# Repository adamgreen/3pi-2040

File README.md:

<br>
My experiments with [Pololu's 3pi+ 2040 robot kit](https://www.pololu.com/product/5004) that was [released on March 7th, 2023](https://www.pololu.com/blog/937/introducing-the-3pi-plus-2040-robot).

## Archived February 4th, 2024
I learned a lot while working on this little bot over the last year. I gained an even better appreciation for the RP2040 microcontroller, got some great mechanical/electronic build ideas from Pololu's cool design, I got the opportunity to port an Arduino library to it, and it even kick started my [MRI-SWD Debug probe](https://github.com/adamgreen/mri-swd#readme) project that I am still actively working on. I think this is a good point to bring my work with this bot itself to an end and I am therefore marking this repository as archived. I will concentrate on other projects instead.

## Notable Page Sections
* [Using Arduino with the 3pi+ 2040](#arduino--3pi-2040)
* [My 3pi+ 2040 Arduino Library](#pololu3piplus2040-arduino-library-port-completed)
* [Debugging 3pi+ 2040 with the Segger J-Link](#debugging-the-3pi-with-segger-j-link)
* [My Notes for Pololu](#my-notes-for-pololu)

## Pololu Links
* [3pi+ 2040 Robot Kit with 30:1 MP Motors (Standard Edition Kit) Pololu Product Page](https://www.pololu.com/product/5004)
* [Pololu 3pi+ 2040 User’s Guide](https://www.pololu.com/docs/0J86)
* [Pololu 3pi+ 2040 Robot Libraries and Example Code on GitHub](https://github.com/pololu/pololu-3pi-2040-robot)

---
## June 6th, 2023
### MRI-SWD Debug Probe Progress
It's been awhile since I had anything to post here but that doesn't mean that I haven't been making progress on a 3π+ 2040 related project. I have spent the last month working on my [MRI-SWD Debug probe](https://github.com/adamgreen/mri-swd#readme). The goal is to use this probe to wirelessly program and debug the RP2040 microcontroller on the 3π+ 2040 robot.

I have the initial prototype far enough along that it can perform basic programming and debugging of RP2040 microcontrollers but only in a breadboard setup. The following shows a sample run of GDB using the programming functionality of the debug probe as it currently exists:

```console
$ arm-none-eabi-gdb -ex "set target-charset ASCII" -ex "set print pretty on" -ex "set remotelogfile mri.log" -ex "target remote 10.0.0.12:2331" -ex "set mem inaccessible-by-default off" test.elf

GNU gdb (Arm GNU Toolchain 12.2 (Build arm-12-mpacbti.34)) 13.1.90.20230307-git
Copyright (C) 2023 Free Software Foundation, Inc.
License GPLv3+: GNU GPL version 3 or later <http://gnu.org/licenses/gpl.html>
This is free software: you are free to change and redistribute it.
There is NO WARRANTY, to the extent permitted by law.
Type "show copying" and "show warranty" for details.
This GDB was configured as "--host=aarch64-apple-darwin20.6.0 --target=arm-none-eabi".
Type "show configuration" for configuration details.
For bug reporting instructions, please see:
<https://bugs.linaro.org/>.
Find the GDB manual and other documentation resources online at:
    <http://www.gnu.org/software/gdb/documentation/>.

For help, type "help".
Type "apropos word" to search for commands related to "word"...
Reading symbols from build/QuadratureDecoder.elf...
Remote debugging using 10.0.0.12:2331
get_absolute_time () at /depots/QuadratureDecoder/pico-sdk/src/common/pico_time/include/pico/time.h:63
63	    update_us_since_boot(&t, time_us_64());
(gdb) load
Loading section .boot2, size 0x100 lma 0x10000000
Loading section .text, size 0x7130 lma 0x10000100
Loading section .rodata, size 0x17c8 lma 0x10007230
Loading section .binary_info, size 0x1c lma 0x100089f8
Loading section .data, size 0x2dc lma 0x10008a14
Start address 0x100001e8, load size 36080
Transfer rate: 47 KB/sec, 5154 bytes/write.
```

### UART Port Adapter

Now that I have the **mri-swd** probe working in a breadboard setup, I want to start down the path of designing PCBs which will allow the debug probe to be attached easily to the 3π+ 2040 robot itself. With that in mind, I have started designing a PCB that attaches to the **Mid Expansion Header** on the 3π+ 2040:
* This PCB routes the UART0 Rx, UART0 Tx, and Ground lines from the 3π+ header to a 6-pin 0.1" header which is compatible with FTDI USB to serial converters, such as this [one from Adafruit](https://www.adafruit.com/product/284).
* This PCB also optionally allows the 3.3V power line of the 3π+ 2040 robot to be connected to the 6-pin FTDI compatible header. Normally this connection isn't needed as the robot will be powered from its own batteries or USB:
  * If used with an actual FTDI adapter then the 3.3V solder jumper on the PCB should be left open circuit so that both the robot and the FTDI adapter don't try to both apply power to the same pin.
  * I also plan to use this 6-pin header for powering and mounting the final **mri-swd** debug probe hardware to the robot. When used for this scenario, the 3.3V solder jumper should be shorted so that the robot's power supply can be used to power the debug hardware as well. Having the **mri-swd** debug probe connected to this header will also allow the probe to expose the UART0 serial traffic on a second WiFi socket.
* The design has been sent off to [OSHPark](https://oshpark.com). I will post again once the PCB arrives and I have it soldered up.

---
## April 22nd, 2023

I received the PCBs from [OSHPark](https://oshpark.com) for my [Debug Port Adapter](hardware/DebugPortAdapter/) this week. A day later I soldered one of them up and now I have a much easier way to connect the [Segger J-Link Debugger](https://www.adafruit.com/product/1369) to my 3π+ 2040. As can be seen above it contains:
* A 10-pin connector that can accept standard SWD debug cables.
* A reset button which is easier to access than the original now under this adapter.
* A power LED which is easier to see than the original now under this adapter.

---
## April 12th, 2023
### Pololu3piPlus2040 Arduino Library Updated to 0.1.2
Over the last week, I have released another 2 updates to the [3π+ 2040 Arduino Library](https://github.com/adamgreen/pololu-3pi-plus-2040-arduino-library). These updates include the following changes:
* 0.1.2 (2023-4-8): Third alpha release from community with a few updates:
  * Moved `Pololu3piPlus2040::BumpSensors::BumpSide` up in namespace to `Pololu3piPlus2040::BumpSide`.
  * Simplify `LineSensors` API to remove `sensorValues` out parameter.
  * Added `RGBLEDs::get()` and `RGBLEDs::getBrightness()` methods to match recent MicroPython library updates.
  * Simplified and fixed a few bugs in my C implementation of the `RGBLEDs::hsv2rgb()` method.
  * Fix buzzer click upon device reset.
  * Fixes to `BumpSensors` class constructor and documentation for `read()` method.
* 0.1.1 (2023-4-4): Second alpha release from community with Motor & Buzzer PWM fixes.

### Start of Pololu3piPlus2040 Arduino Library version 0.2.x
I have started working on a [0.2.x branch](https://github.com/adamgreen/pololu-3pi-plus-2040-arduino-library/tree/v0.2.x) of the 3π+ 2040 Arduino Library. This branch is an attempt to start leveraging [Pololu's Pico-SDK based C library for the 3π+ 2040 robot](https://github.com/pololu/pololu-3pi-2040-robot/tree/master/c). This should allow the Arduino Library to just become a lightweight C++ inline wrapper around this C API developed by Pololu.

### My 3π+ 2040 Bot has a Littermate
<br>
I received a second [3π+ 2040 Robot Kit](https://www.pololu.com/product/5004) today. This kit was purchased with the early adopters discount from Pololu described below in a quote from the 3π+ 2040 product page:

>Early adopters who publicly share their 3pi+ 2040 experiences will be eligible for an additional robot with an extra $25 discount.

### Next Steps
* Attempt to design a wireless debugging/programming solution for the 3π+ 2040 robot.

---
## April 6th, 2023
### Debug Port Adapter

My current method of connecting the J-Link debugger to my 3pi+ 2040 is a bit hacky with taped together Dupont wires. Can I make something a bit better?

My answer to that question was to design an [adapter PCB in KiCAD](hardware/DebugPortAdapter/) that makes the J-Link connection easier:
* Adapts the 6-pin debug header included by Pololu on the 3pi+ 2040 to the more standard 2x5 pin SWD debug connector.
* This PCB will obscure the green power LED currently on the robot so I have included a LED that lights up when the 3.3V pin on th header is powered up.
* This PCB also makes it even more difficult to reach the reset button on the robot so I have included a reset button as well.
* I plan to design a part to be 3D printed and glued to the back of this PCB to add some support behind the SWD connector and the reset button.
* The design has been sent off to [OSHPark](https://oshpark.com). I will post again once the PCB arrives and I have it soldered up.

---
## April 5th, 2023
### Pololu3piPlus2040 Arduino Library Port Completed

I have completed the initial port of my [3pi+ 2040 Arduino Library](https://github.com/adamgreen/pololu-3pi-plus-2040-arduino-library). All of the features of the 3pi+ 2040 are now supported by the library and test out well on my bot.

**Features that I completed since my last update here:**
* **Buttons** - Had to take into account that all of the button pins do double duty so code had to be written to carefully multiplex between these pin roles.
* **Encoders** - Used PIO for the RP2040 port like Pololu did in their MicroPython library. Rather than port the PIO code from the MicroPython library, I just used my existing [QuadratureDecoder code](https://github.com/adamgreen/quadraturedecoder)
* **IMU** - The Gyro/Accelerometer used on the 3pi+ 2040 has a different part number than the 3pi+ 32U4 but the only difference I found was the response to the I2C WHO_AM_I request.
* **Line Sensors** - Most of the work for this was already done for the PIO based bump sensor driver.
* **Motors**

The list of supported classes now includes:
* Pololu3piPlus2040::ButtonA
* Pololu3piPlus2040::ButtonB
* Pololu3piPlus2040::ButtonC
* Pololu3piPlus2040::Buzzer
* Pololu3piPlus2040::Encoders
* Pololu3piPlus2040::OLED
* Pololu3piPlus2040::Motors
* Pololu3piPlus2040::LineSensors
* Pololu3piPlus2040::BumpSensors
* Pololu3piPlus2040::IMU
* Pololu3piPlus2040::RGBLEDs
* Pololu3piPlus2040::ledYellow()
* Pololu3piPlus2040::readBatteryMillivolts()

---
## March 31st, 2023
### Arduino & 3pi+ 2040

The latest Arduino IDE already ships with a board package that is compatible with the 3pi+ 2040: **Arduino Mbed OS RP2040 Boards**. The circuit of the 3pi+ 2040 PCB is close enough to the Raspberry Pi Pico that it just worked:
* The **W25Q128JVP**  16MB flash part used on the 3pi+ 2040 PCB seems to be similar enough to the **W25Q16JVUXIQ** 2MB flash part used on the Pico that the second stage bootloader linked into Arduino binaries just work. *If someone knows that I should be using a different second stage bootloader with this device, please let me know.*
* The yellow LED on the 3pi+ 2040 is even connected to the same pin as the user LED on the Pico, **Pin 25**. This means that the stock **Blink** Arduino example just worked on the 3pi+ 2040 as well.

### Uploading Code from Arduino IDE to 3pi+ 2040
The Arduino IDE was able to successfully upload new code to the 3pi+ 2040 over the same USB connection as used for MicroPython programming. There are 2 ways that the Arduino IDE can upload code to the RP2040 microcontroller using the USB cable:
* Once you have Arduino code up and running on your RP2040, the IDE can use USB to make a serial connection to the device. This means that `Serial.print()` calls in your code will show up in Arduino's *Serial Monitor*. Arduino can use this same USB serial connection to place the RP2040 into bootloader mode automatically. The user just needs to select the **Sketch/Upload** option in the Arduino IDE and it will build and deploy the code to your 3pi+ 2040 robot with no manual intervention from you. The image below shows the 3pi+ 2040 robot showing up as a **Rasperry Pi Pico** on the **dev/cu.usbmodem1101** virtual serial port when connected to my Mac.

* The previous automatic upload process doesn't always work though. If the Arduino USB serial driver isn't successfully running on your 3pi+ 2040 then you will need to place the RP2040 into bootloader mode manually before starting the upload process in Arduino.All you need to do is hold down the **B Button** while cycling the **Reset Button**. This will force the RP2040 into bootloader mode where it shows up on your PC as a **RPI-RP2** drive. Once this special drive shows up on your PC, you can just select the **Sketch/Upload** option in the Arduino IDE as usual. When is this slightly more manual process required?
  * If your 3pi+ 2040 robot is currently running MicroPython. The Arduino USB serial driver isn't running on your bot so it can't be used. **Note:** *Switching to Arduino code from MicroPython will delete your custom MicroPython programs from the 3pi+ 2040. Make backup copies of your MicroPython code before uploading Arduino code to the robot.*
  * If your Arduino robot code hangs so bad that the Arduino USB serial driver can't run on the robot.

If you want to switch back to MicroPython after experimenting with Arduino on your 3pi+ 2040 then you can follow the steps in the [Pololu 3pi+2 2040 User's Guide](https://www.pololu.com/docs/0J86/5.1) to reupload the MicroPython firmware.

### Porting the Pololu3piPlus32U4 Arduino Library

Once I knew that Arduino was going to be relatively easy to use with the 3pi+ 2040, I turned my attention to [Pololu's existing Arduino Library for the ATmega32U4 based 3pi+](https://github.com/pololu/pololu-3pi-plus-32u4-arduino-library). What would it take to start porting this library to run on the 2040 based board instead? It turns out not much and quite a bit at the same time. A lot of the functionality that you would want to expose from a library is the same between the two versions. The biggest obstacle was AVR specific code that was written for the library to get the most performance possible on the 32U4 based board:
* The FastGPIO library is used a lot in the 32U4 library. I replaced this with a RP2040SIO library instead. It takes the methods exposed by Pololu's FastGPIO library and implements them using the RP2040's fast SIO registers instead.
* I came across several places in the 32U4 code which contained inline AVR assembly language. I removed this code and replaced it with corresponding C/C++ code which is probably fast enough on a 125MHz 32-bit ARM Cortex-M0 core.
* The OLED driver was written to use the FastGPIO library and bit twiddling to implement the required SPI protocol rather than the SPI peripheral itself. I created a RP2040SPI library that exposes a SharedSPI class. This SharedSPI class makes use of the SPI peripheral on the RP2040 but is able to switch the SCLK and baud rates on the fly when switching between sending data to the OLED and the addressable RGB LEDs. This is functionality I stole from Pololu's 3pi+ 2040 MicroPython library as it does the same.
* The buzzer code was tied very tightly to the Timer hardware on the AVR. In my RP2040 port, I just used the existing **mbed::Timeout** and **mbed::PWM** C++ objects available from the Arduino mbed core for ARM microcontrollers.

Other changes I made as part of the port so far:
* I modified some of the samples to make use of the addressable LEDs since the RP2040 version of the 3pi+ doesn't have the red and green LEDs of the 32U4 version but it does have six addressable LEDs instead.
* I rewrote the light sensor reading code to use the really cool PIO (Programmable I/O) peripheral on the RP2040 as used by Pololu's MicroPython driver as well. I actually ported Pololu's PIO code and integrated it into a C++ based driver. I did track down a bug in the MicroPython driver and fixed it while working on this port:
  * Originally the Pololu code would have the PIO code start the charging phase at the end of the previous read.
  * The CPU was responsible for kicking off the next read by the PIO.
  * The PIO would then start the discharge phase and start timing the discharge for each light sensor pin.
  * Depending on what the CPU was used to do after the previous read completed and before starting the next read, the capacitors may have ended up with a different level of charge and this would impact the time it took to discharge.
  * The PIO code should be responsible for the timing of the charging phase as well the discharging phase or the readings can be inconsistent.
* The Arduino IDE isn't able to assemble PIO assembly language sources. I have checked in the **.pio** source code and the **.pio.h** header files generated by **pioasm**. This way the pre-assembled output can be used by the Arduino process while the originals are still available in the tree as well. I have a Makefile in the `pio\` folder which can be used to install the Pico C SDK and assemble the PIO assembly language source files. This may only work on macOS though.

At this point I only have a portion of the library ported but I thought I would commit what I have so far to my [3pi+ 2040 Arduino Library GitHub Repository](https://github.com/adamgreen/pololu-3pi-plus-2040-arduino-library) so that I can share my current progress and solicit some feedback.

**Features/Examples that have been ported so far:**
* Only 2 examples have been ported so far: **BlinkLEDs** and **BumpSensorTest**.
* **OLED Display** driver.
* LED driver. This includes the **Yellow LED** shared with the 32U4 version and the 6 addressable **RGB LEDs** that are new for the 2040 version.
* **Bump Sensor** driver.
* **Buzzer** driver.

**Features to be ported in the near future:**
* **Buttons**
* **Encoders** - Will use PIO for the RP2040 port like Pololu did in their MicroPython library.
* **IMU**
* **Line Sensors** - Most of the work for this has already been done for the PIO based bump sensor driver.
* **Motors**

I also created a [PR in the Pololu 3pi+ 2040 repository](https://github.com/pololu/pololu-3pi-2040-robot/pull/1) with my proposed change to the PIO code for the QTR read path.

### Debugging the 3pi+ with Segger J-Link

I didn't get that far into the Arduino library porting before I hit an issue that I really wanted to debug. I have a wireless debugging solution as a future project in mind for the 3pi+ 2040 but that is the future and I had some debugging that I wanted to do right now. Time to pull out my trusty [Segger J-Link Debugger](https://www.adafruit.com/product/1369) and wire it up to my robot. I had previously soldered a 1x6 0.1" header onto the 3pi+'s debug port while putting the kit together. I just needed to use 5 male to male Dupont wires to connect up the necessary signals between the robot and the debug adapter. The end product wasn't pretty but it worked. My drawing below might make the required wiring a bit clearer.

<br>
**Image Portion Credits:**
* [3pi+ Pinout from Pololu's 3pi+ 2040 Control Board Pinout and Peripherals](https://www.pololu.com/file/0J1941/3pi-2040-control-board-pinout.pdf)
* [Legacy JTAG Pinout from ARM's Cortex-M Debug Connectors](https://documentation-service.arm.com/static/5fce6c49e167456a35b36af1)

The command line I used to start the Segger J-Link GDBServer up on my MacBook Air for debugging the RP2040 microcontroller on the robot:
```console
JLinkGDBServer -device RP2040_M0_0 -nohalt -endian little -if SWD -speed 12000 -localhostonly
```

The comand line I use to launch GDB to connect to the J-Link GDBServer and debug the Arduino built binary:
```console
arm-none-eabi-gdb -ex "set target-charset ASCII" -ex "set print pretty on" -ex "target remote :2331" -ex "set mem inaccessible-by-default off" *.ino.elf
```
I run the above command line in the build output directory used by the Arduino build IDE. This directory can be found in the Arduino Output window after a build if the "Show verbose output during:" "compile" box has been checked.

The version of the Segger J-Link debugger that I used is no longer sold by Adafruit but you can still buy the [SEGGER J-Link EDU Mini - JTAG/SWD Debugger](https://www.adafruit.com/product/3571) and it works just as well. *It must be noted that these EDU versions are to be used for **non-commercial** purposes only.*

### Next Steps
* ~~Finish my [3pi+ 2040 Arduino Library port](https://github.com/adamgreen/pololu-3pi-plus-2040-arduino-library).~~
* ~~Use KiCAD to design a PCB that adapts the 3pi+ 2040 debug port to ARM's standard 10-pin SWD connector. This will allow me to get rid of my current cabling hack.~~

---
## March 27th, 2023
### Behavior Based Robot Code in MicroPython

Now that I am more comfortable with using [Pololu's MicroPython library](https://github.com/pololu/pololu-3pi-2040-robot/tree/master/micropython_demo) for programming the 3pi+ 2040 robot, I decided I would take the plunge and port some of the behavior based robot code from ["Mobile Robots: Inspiration to Implementation" by Joseph L. Jones and Anita M. Flynn](https://www.amazon.com/Mobile-Robots-Inspiration-Implementation-Second/dp/B0087P7X2S). I ended up porting the **Cruise** and **Escape** behaviors but I had to skip the **Follow** and **Avoid** behaviors since the 3pi+ robot doesn't have photoresistor or IR proximity sensors. The RugWarrior code from the book was written in IC (Interactive C) which supports multiple processes (threads) for running the various behaviors at the same time. For my MicroPython code I ended up implementing the behaviors as state machines and updating them at regular intervals (50Hz). The state machine doesn't really need to do anything for the **Cruise** behavior since it just wants to keep driving forward at a slow rate. The **Escape** state machine is a bit more complicated as this is a ballistic behavior which takes control for some time while it backs the robot up and then executes the needed turn.

The code for my MicroPython port can be found in [behave.py](micropython/behave.py). I have to ask the forgiveness of any experienced Python programmers who read my MicroPython code. I have very little Python experience and its shows in my code.

Having access to MiroPython on the 3pi+ 2040 robot and the MicroPython code provided by Pololu made it quite simple for me to get up and running on this robot. It was easy to find sample code that did close to what I wanted and then start modifying from there. It was also straightforward to get new code on the device (through the USB mass storage drive exposed from the robot or using [rshell/rsync](https://github.com/dhylands/rshell)).

### Next Steps
* ~~Investigate what it would take to use [Arduino's RP2040 port](https://github.com/arduino/ArduinoCore-mbed) with the 3pi+ robot.~~
* ~~Connect my [Segger J-Link debug adapter](https://www.adafruit.com/product/3571) up to my 3pi+ robot to enable programming and debugging of Arduino C/C++ code on the bot.~~

---
## March 24th, 2023
### Pololu's 3pi+ 2040 MicroPython Library
I spent some time earlier this week looking at the [MicroPython libraries and samples provided by Pololu up on GitHub](https://github.com/pololu/pololu-3pi-2040-robot). I saw some interesting features of note while looking at Pololu's MicroPython code:
* They use PIO to read the wheel's quadrature decoders in the background like I did with [my encoder library](https://github.com/adamgreen/QuadratureDecoder).
* They use PIO to use RC (resistor capacitor) discharge times to read the analog sensor values for the 5 downward facing line sensors and the 2 front bumper switches.
* Display driver is optimized to only need to send over pages that have been dirtied in the frame buffer since the last time it was copied to the device over SPI.
* Buzzer library takes a string of notes to be played in the background while the robot is doing other things. The string used reminds me of the GW-BASIC ```PLAY``` command from my youth.

After looking through the Pololu code I now have a much better idea of how to write my own MicroPython code for the robot.

### Reading Assignment

I have decided that one of my first 3pi+ projects will be to write a behavior based program in MicroPython. With that in mind I have gone back and reread the software sections of ["Mobile Robots: Inspiration to Implementation" by Joseph L. Jones and Anita M. Flynn](https://www.amazon.com/Mobile-Robots-Inspiration-Implementation-Second/dp/B0087P7X2S). The 3pi+ doesn't have the same sensors as the RugRover bot covered by this book but I think I can still make an interesting port of their sample program from Appendix B none the less.

### MicroPython Development Setup
Rather than using a Python specific IDE like [Thonny](https://thonny.org) or [Mu](https://codewith.mu), I decided to use [Visual Studio Code](https://code.visualstudio.com) for editing my MicroPython based robot code and [Dave Hyland's rshell utility](https://github.com/dhylands/rshell) for deploying it over to the 3pi+ 2040 robot. I even created a [deploy script](deploy) to make this process even easier. The contents of that script are simply:
```shell
#! /usr/bin/env bash
rshell -p /dev/tty.usbmodem1101 --buffer-size 512 rsync micropython/ /pyboard/
```
It uses the ```rsync``` command to find the python scripts which I have updated on my machine and automatically copies them over to the robot.

### First MicroPython Tests
I wrote my first 2 little MicroPython test programs for the 3pi+ 2040 to get better acquainted with the library that Pololu has put together:
* [bump_test.py](micropython/bump_test.py): This test program continuously shows the analog readings from the 2 front bumpers. It can be used to see ambient lighting effects on light sensors used as part of the bumper setup on the 3pi+ 2040 robot. I was wondering if these front facing light sensors would be sensitive enough to ambient lighting to implement a **Follow** behavior as described in the [Mobile Robots](https://www.amazon.com/Mobile-Robots-Inspiration-Implementation-Second/dp/B0087P7X2S) book. After running this test program on my bot it does look like the sensor measurements do change based on the amount of ambient light but not by very much and certainly not with enough disparity between the two sensors to determine the direction of the light source. No **Follow** behavior for me.
* [motion_test.py](micropython/motion_test.py): This test program runs both motors at 100% power in the forward direction to observe the maximum encoder ticks per second rate. When running this test on the actual robot, I saw the maximum rate was always over 5000 encoder ticks per second. Such rates were seen when the robot was lifted up off the ground and when it was down running on carpeted flooring. **5000 ticks/second** will therefore be the maximum velocity allowed by any PID code that I write in the future.

---
## March 15th, 2023
### Notching for Debug Header

I installed a 1x6 female 0.1" header on the debug port while soldering parts down to the control board. Unfortunately I didn't have low-profile headers like Pololu used for the included OLED and this resulted in the header not fitting underneath the top edge of the plastic bumper skirt. I also think the top of the skirt would make it hard to connect anything to this header even if I had used a low profile version. I used an X-Acto knife and filing board to cut a notch in the top of the skirt to make room for my taller debug header and allow the skirt to properly clip down around the right motor. The plastic wasn't that hard and didn't put up much of a fight during this process. It only took a few minutes.

### Shared Project Possibility from Personal Robotics Discord
This new [3pi+ 2040 Robot](https://www.pololu.com/product/5004) was first brought to my attention on the Personal Robotics Discord server last week and a few of the members, including myself, ordered one. We started receiving them and discussing them on Discord this week. One of the recent topics has been the ability to run MicroPython code on the robot. This ability has been well received by the group. @shurik179 [Island Robotics] mentioned that he has some IMU sensor fusion C code that he has run on robots in the past and was wondering if the RP2040 would have enough grunt to run such math heavy code from within the MicroPython interpreter. This made me think of a potential fun and challenging project for me to work on:
* Take what I learned from my [i2cperipheral project](https://github.com/adamgreen/i2cperipheral#readme) and apply it to building a native MicroPython library to implement the sensor fusion code used by shurik179. Maybe this library could even take advantage of the RP2040's second core to run this sensor fusion code in the background?

### Inside 3pi+ 2040 MicroPython
I have also started looking at the code included with Pololu's custom MicroPython image. This has me looking at the following Pololu repositories up on GitHub:
* https://github.com/pololu/pololu-3pi-2040-robot
* https://github.com/pololu/micropython-build
* https://github.com/pololu/micropython/tree/3pi

---
## March 14th, 2023
### 3pi+ 2040 Robot Kit Arrived Today

My [Pololu 3pi+ 2040 Early Adopter Robot Kit](https://www.pololu.com/product/5004) arrived via UPS earlier this afternoon. Upon opening the robot kit I found a welcome letter from Pololu, thanking the early adopters for ordering their first RP2040 based robot and asking for feedback. This repository is my answer for that feedback request.

The kit was very well packed. The box is quite rigid and ready to take on the typical handling dealt out by UPS/Fedex/USPS employees. The robot parts inside the box were well wrapped in multiple bubble wrap bags. The following photo shows the kit parts laid out on my living room floor, mere minutes after it arrived at my front door.

### Kit Assembly
I started reading and following the assembly instructions from [Chapter 3](https://www.pololu.com/docs/0J86/all#3) of the [Pololu 3pi+ 2040 User’s Guide](https://www.pololu.com/docs/0J86) so that I could see my new little bot up and running by the end of the day. I skipped the assembly video and just jumped into the written instructions since that is just more compatible with how my mind works.

#### Initial PCB Test

#### Some Photos Taken During the Assembly Process

#### Included MicroPython Samples
Once I completed the assembly of the robot I booted it up and ran through the MicroPython samples preinstalled by Pololu. The following animation shows the spin.py sample running on my newly assembled robot.

### Next Steps
* ~~I installed a 1x6 female 0.1" header on the debug port while soldering parts down to the control board. Unfortunately I didn't have low-profile headers like Pololu used for the included OLED and this resulted in the header not fitting underneath the top edge of the plastic bumper skirt. I will need to cut a notch in the top of this skirt to make room for my taller header and allow the skirt to properly clip down around the right motor.~~<br>

* ~~Explore the MicroPython support on the robot a bit more and try writing some code to have it bounce around and explore its new home.~~
* ~~Dream up additional future projects for this cool little bot.~~

---
## March 8th, 2023
<br>
I saw a link for this new [Pololu 3pi+ 2040 Early Adopter Robot Kit](https://www.pololu.com/product/5004) show up on the **Personal Robotics** Discord Server yesterday and it really caught my eye:
* I really like the look of it. It reminds me of the [RugRover project](https://github.com/adamgreen/rugrover#readme) that I have been working on recently but much nicer than anything I could design myself.
* I also like that it uses the RP2040 microcontroller as its brain. I have done some experimenting in the past with the RP2040. Some of my previous RP2040 projects include:
  * https://github.com/adamgreen/i2cperipheral
  * https://github.com/adamgreen/QuadratureDecoder
* Gives me an opportunity to continue with a little bit more MicroPython exploration and then go deeper into C/C++ programming of the RP2040.
* Quite a bit of bang for the buck.

In the end I decided it looked so cool that I purchased one this evening and started this GitHub repository to document my time with the bot once it arrives.

## My Notes for Pololu
If anyone at Pololu ever happens to read the dribble I post here then this sections lists some comments/notes that I have based on my early adopter experience:
* Cool bot!
  * I love the look of the 3pi+ bots.
  * The RP2040 is a very cool microcontroller and really nice to see it now available on the 3pi+ series of Pololu robots.
  * One advantage of using the RP2040 over the AVR is the ability to run MicroPython on the robot. I think this will make the 3pi+ series of robots accessible to even more robot builders/programmers.
* Would be good if the [Pololu 3pi+ 2040 User’s Guide](https://www.pololu.com/docs/0J86) noted its last update date/time somewhere since it is currently under construction. This would allow early adopters know if and when we should go back and read any new content and/or updates made since the last time we read it.
* ~~In section 1.1 of the [User’s Guide](https://www.pololu.com/docs/0J86) it contains the following part description, "two 1/4″ #2-56 standoffs <u>(OLED version only)</U>". The OLED note in parenthesis isn't required as the 3pi+ 2040 only ships with the OLED.~~ *Fixed as of March 25, 2023.*
* The debug port is too close to the edge of the bumper skirt. It is difficult to fit the header and any required cabling without notching the skirt. That said it isn't too hard for the user to make this notch themselves.
* The buttons on the 3pi+ 2040 control board are awfully small and can be tricky to press, especially the reset button.
* ~~If you don't solder on headers for the expansion ports while building up the kit, it would be tricky to do it later as this will require desoldering the motor and battery connections so that the bottom battery compartment can be removed from the PCB.~~

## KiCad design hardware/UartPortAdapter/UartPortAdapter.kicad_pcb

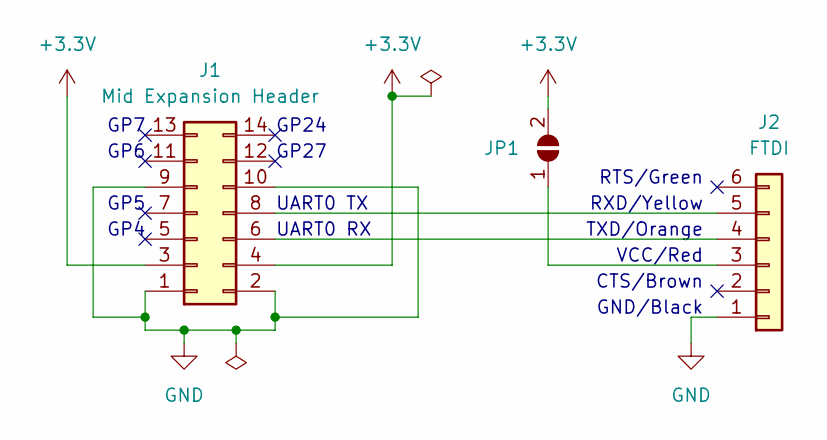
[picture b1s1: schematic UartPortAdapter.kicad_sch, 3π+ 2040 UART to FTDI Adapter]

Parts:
J1: Mid Expansion Header; PinHeader_2x07_P2.54mm_Vertical
J2: FTDI; PinHeader_1x06_P2.54mm_Vertical
JP1: SolderJumper_2_Open; SolderJumper-2_P1.3mm_Open_TrianglePad1.0x1.5mm

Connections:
+3.3V: J1.3, J1.4, JP1.2 (B)
GND: J1.1, J1.2, J1.9, J1.10, J2.1
unnamed: J1.6, J2.4
unnamed: J1.8, J2.5
unnamed: J2.3, JP1.1 (A)

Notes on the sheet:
UART0 RX
GP27
GND/Black
GP5
UART0 TX
VCC/Red
RTS/Green
GP24
CTS/Brown
TXD/Orange
GP6
GP4
GP7
RXD/Yellow

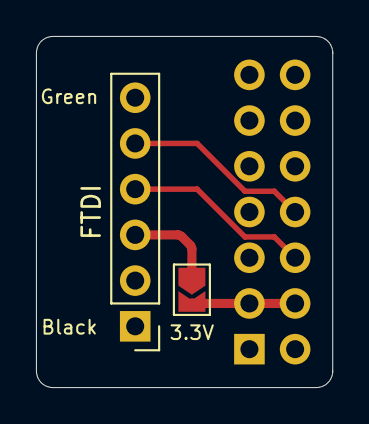
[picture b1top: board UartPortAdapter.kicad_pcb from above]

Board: 2 copper layers, 16.5 x 19.5 mm, 3 parts (1 on the bottom side), 5 nets.

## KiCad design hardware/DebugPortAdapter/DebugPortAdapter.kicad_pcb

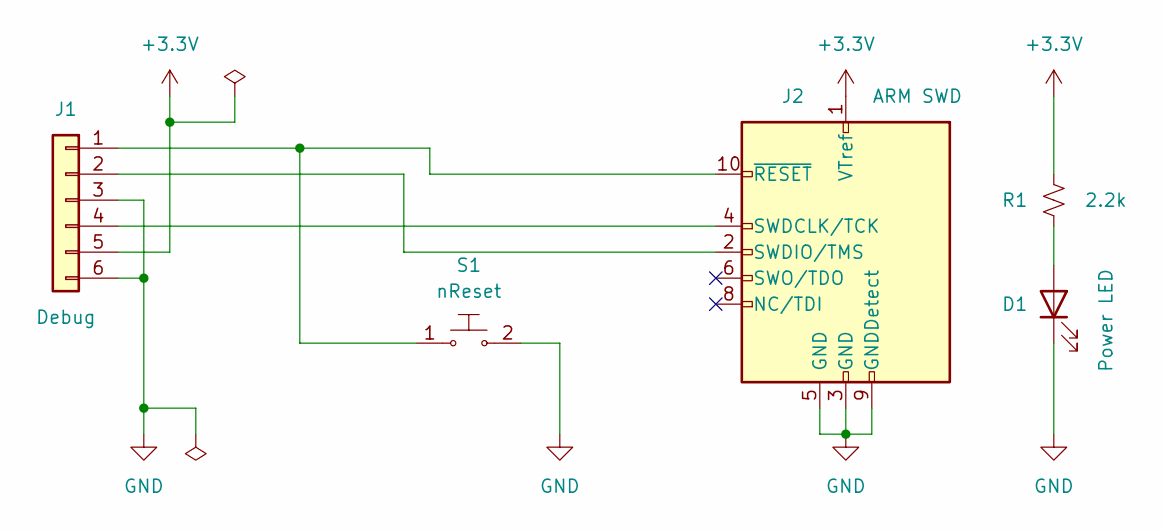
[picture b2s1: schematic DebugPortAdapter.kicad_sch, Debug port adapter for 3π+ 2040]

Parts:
D1: Power LED; LED_1206_3216Metric_Pad1.42x1.75mm_HandSolder
J1: Debug; PinHeader_1x06_P2.54mm_Vertical
J2: ARM SWD; CON10_2X5_DUK_FTSH_SAI
R1: 2.2k; R_0805_2012Metric_Pad1.20x1.40mm_HandSolder
S1: nReset; SW_Push_1P1T_NO_6x6mm_H9.5mm; MPN GPTS203211B; Digi-Key_PN CW181-ND

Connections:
+3.3V: J1.5, J2.1 (VTref), R1.1
GND: D1.1 (K), J1.3, J1.6, J2.3 (GND), J2.5 (GND), J2.9 (GNDDetect), S1.2
unnamed: D1.2 (A), R1.2
unnamed: J1.1, J2.10 (~RESET), S1.1
unnamed: J1.2, J2.2 (SWDIO/TMS)
unnamed: J1.4, J2.4 (SWDCLK/TCK)

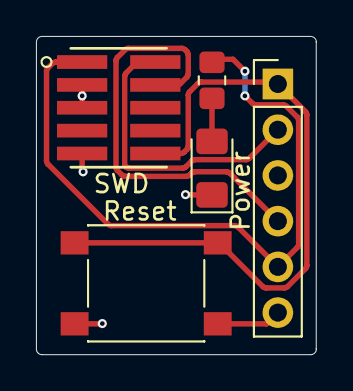
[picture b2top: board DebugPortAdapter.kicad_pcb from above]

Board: 2 copper layers, 15.5 x 17.7 mm, 5 parts (0 on the bottom side), 6 nets.

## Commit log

2023-03-10 Initial commit
    Includes initial March 8th notes.
2023-03-15 Add March 14th notes
    The robot kit arrived today and I put it together. Still need to try
    programming it.
2023-03-15 March 15th Notes
    * I notched out the skirt to fit the debug header.
    * Potential future native MicroPython library project.
    * Additional notes to Pololu.
2023-03-25 Updated README with March 24th notes
    * Looked at the Pololu MicroPython code for the 3pi+ 2040 robot.
    * Reread the software sections of the "Mobile Robots" book to refresh my
    memory of how they implemented their behavior based samples.
    * Implemented my first 2 little MicroPython test programs.
2023-03-28 Add behavior sample
    Updated README with my notes about this code as well.
2023-03-31 Update README with March 31st notes
    * Got Arduino working with the 3pi+ 2040 robot.
    * Started porting Pololu's 3pi+ 32U4 Arduino Library to the RP2040
    version.
    * Got my Segger J-Link debug adapter working with the 3pi+ 2040.
2023-04-01 Add links to README
2023-04-05 Update README with April 5th notes
    I finished porting the Arduino library to the 3pi+ 2040.
2023-04-05 Add link to README
2023-04-06 Added DebugPortAdapter PCB design
    This debug port adapter will make it easier to connect my J-Link debug
    hardware to the 3pi+ 2040.
    I have provided more information about this PCB in the README updates
    added as part of this commit.
2023-04-13 Update README with April 12th notes
    * Released 0.1.1 and 0.1.2 updates to my 3π+ 2040 Arduino Library.
    * Started work on a 0.2.x branch which will attempt switching the
    Arduino Library over to using Pololu's C API for the 3π+ 2040.
    * Discounted 3π+ 2040 robot kit arrived.
2023-04-22 Update README with April 22nd notes
    I received the PCBs for the debug adapter board that I designed for the
    3π+ 2040 robot. It includes a 10-pin connector to accept standard SWD
    debug cables, easy to access reset button, and unobscured power LED.
2023-06-06 Add UART adapter PCB
    This PCB routes the UART0 pins on the 3π+ 2040's 2x7 Mid Expansion
    Header out to a 6-pin FTDI compatible header. This allows for a FTDI
    adapter to be used on the robot to check the UART signals from the GP28
    and GP29 pins. I also plan to use this header configuration for getting
    power and serial connectivity to my MRI-SWD debug probe in the future.
    Having access to the serial pins will allow it to expose the serial
2023-07-15 Fixed the UART adapter PCB
    The 0.1" 2x7 Mid Expansion header was flipped left to right. I noticed
    this issue when testing revision 0.1.0 of the PCB.
    This updated version has been sent off to OSHPark for manufacture.
2024-02-05 Marking project as archived

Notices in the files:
hardware/DebugPortAdapter/DebugPortAdapter.kicad_sch:
CC BY-SA 4.0
